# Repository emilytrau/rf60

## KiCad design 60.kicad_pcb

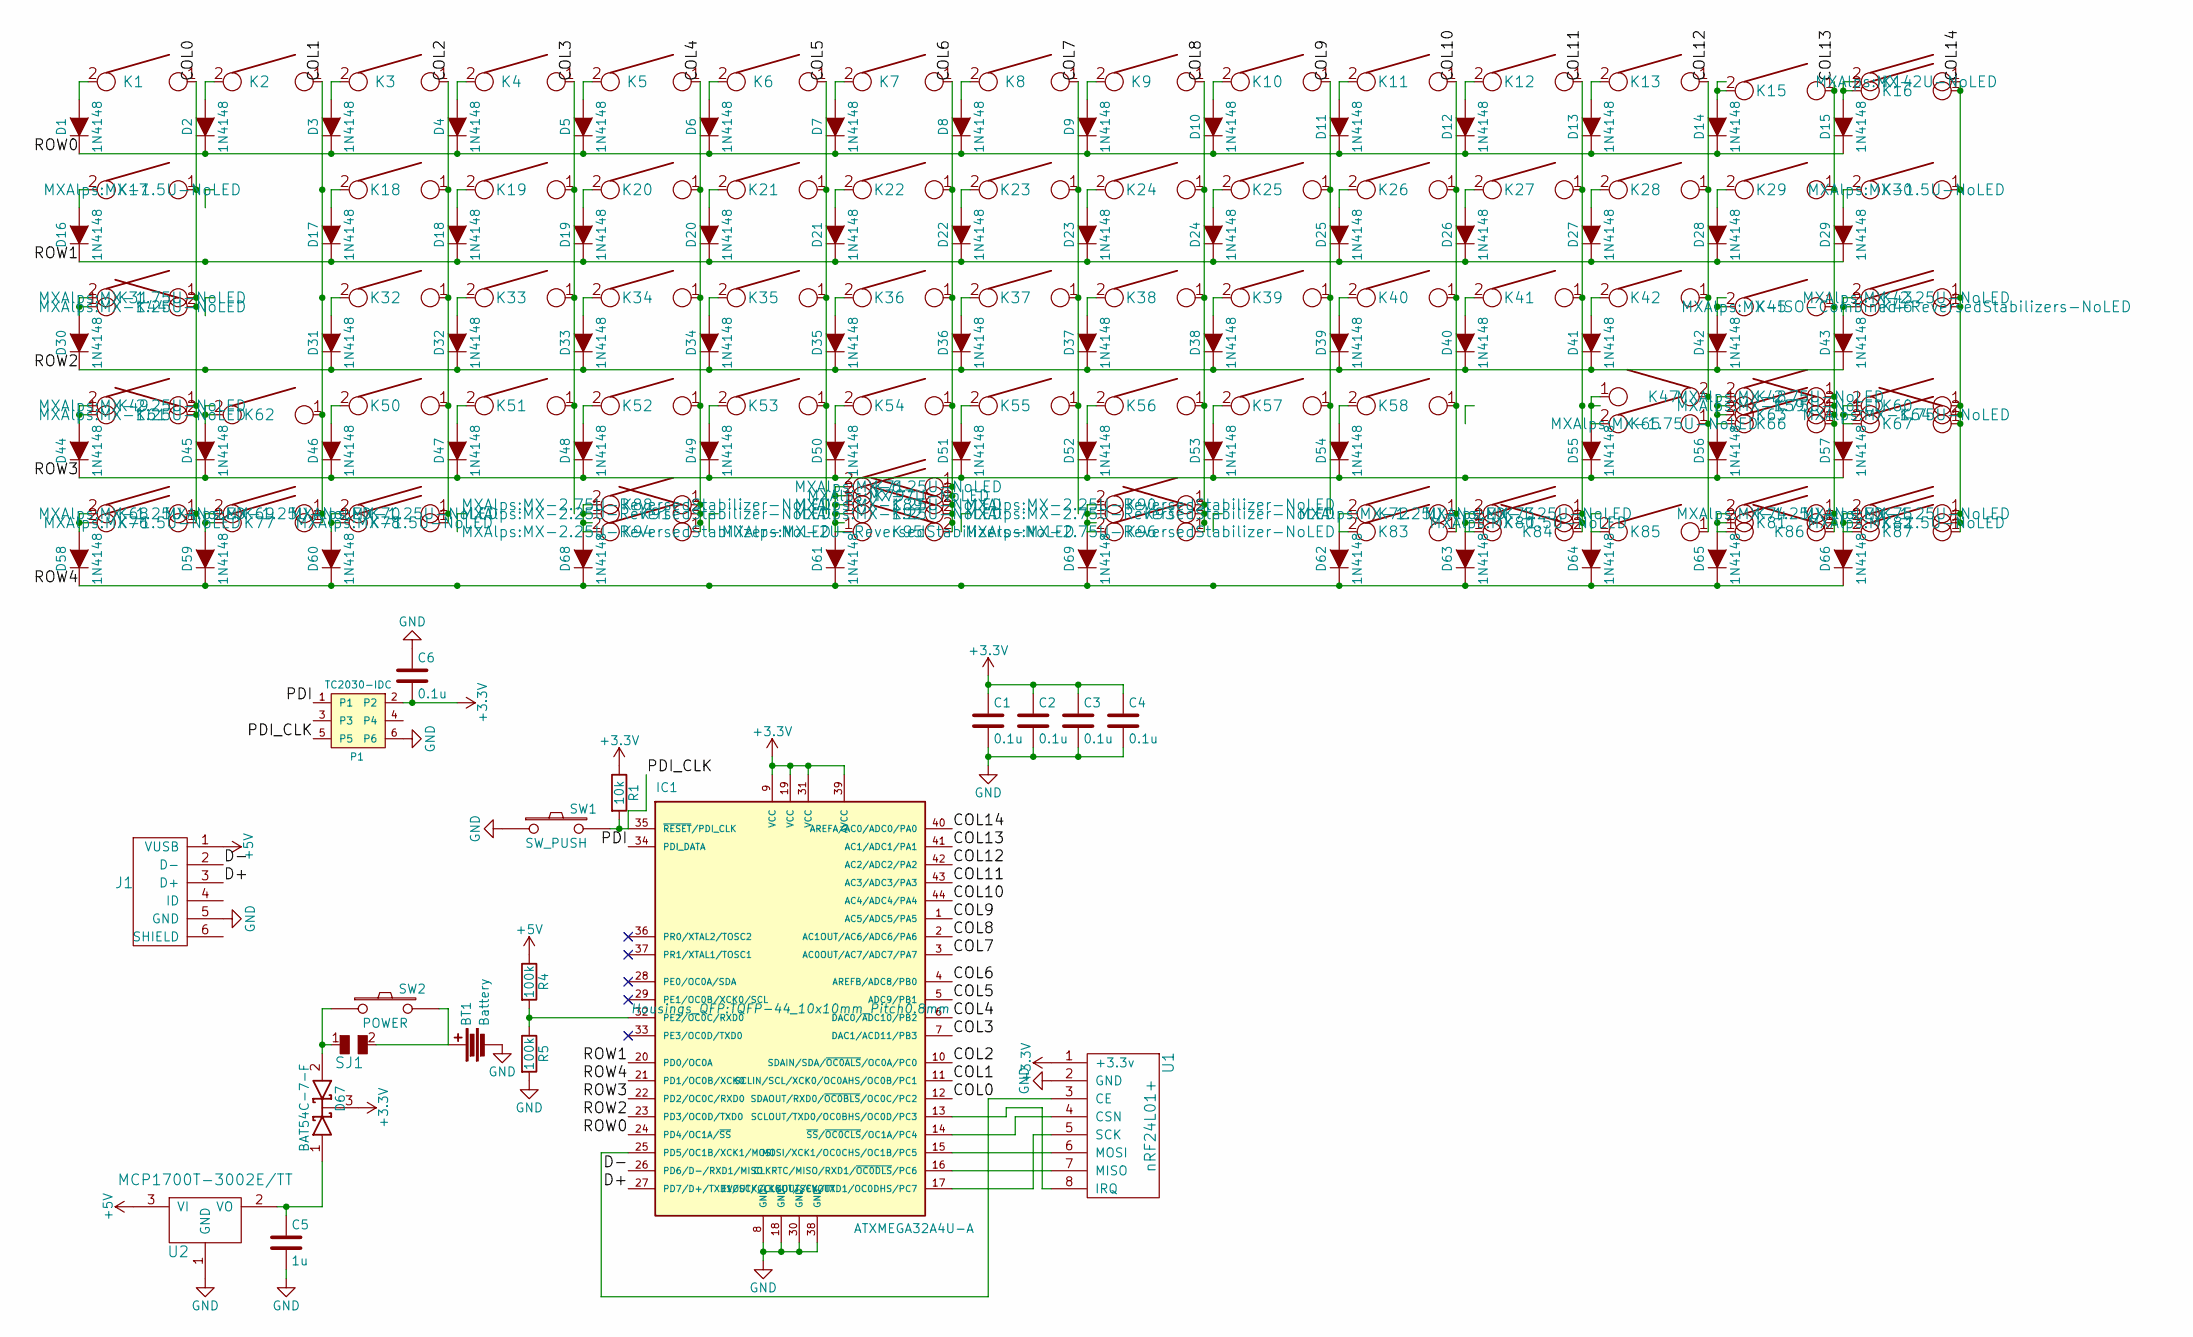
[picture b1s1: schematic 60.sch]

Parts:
BT1: Battery; CR2032_BK-913
C1, C2, C3, C4, C6: 0.1u; C_0805_HandSoldering
C5: 1u; C_0805_HandSoldering
D1, D2, D3, D4, D5, D6, D7, D8, D9, D10, D11, D12, D13, D14, D15, D16, D17, D18, D19, D20, D21, D22, D23, D24, D25, D26, D27, D28, D29, D30, D31, D32, D33, D34, D35, D36, D37, D38, D39, D40, D41, D42, D43, D44, D45, D46, D47, D48, D49, D50, D51, D52, D53, D54, D55, D56, D57, D58, D59, D60, D61, D62, D63, D64, D65, D66, D68, D69: 1N4148; D_SOD-323_HandSoldering
D67: BAT54C-7-F; SOT-23_Handsoldering
IC1: ATXMEGA32A4U-A; TQFP-44_10x10mm_Pitch0.8mm
J1: USB_mini_micro_B; USB_miniB_hirose_5S8
K1, K2, K3, K4, K5, K6, K7, K8, K9, K10, K11, K12, K13, K15, K16, K18, K19, K20, K21, K22, K23, K24, K25, K26, K27, K28, K29, K32, K33, K34, K35, K36, K37, K38, K39, K40, K41, K42, K45, K47, K50, K51, K52, K53, K54, K55, K56, K57, K58, K60, K62, K63, K66, K67, K77, K81, K83, K84, K85, K86, K87: KEYSW; MX-1U-NoLED
K14: KEYSW; MX-2U-NoLED
K17, K30, K76, K78, K80, K82: KEYSW; MX-1.5U-NoLED
K31, K59, K64, K65: KEYSW; MX-1.75U-NoLED
K43, K49: KEYSW; MX-2.25U-NoLED
K44, K61, K68, K69, K70, K72, K73, K74, K75, K89, K92: KEYSW; MX-1.25U-NoLED
K46: KEYSW; MX-ISO-Combined-ReversedStabilizers-NoLED
K48: KEYSW; MX-2.75U-NoLED
K71: KEYSW; MX-6.25U-NoLED
K79: KEYSW; MX-7U-NoLED
K88, K93, K96: KEYSW; MX-2.75U-ReversedStabilizer-NoLED
K90, K91, K94: KEYSW; MX-2.25U-ReversedStabilizer-NoLED
K95: KEYSW; MX-2U-ReversedStabilizers-NoLED
P1: TC2030-IDC; TC2030-NL_SMALL
R1: 10k; R_0805_HandSoldering
R4, R5: 100k; R_0805_HandSoldering
SJ1: SOLDER_JUMPER; SOLDER_JUMPER_2
SW1: SW_PUSH; SW_SPST_TL3342
SW2: POWER; Pin_Header_Straight_1x02_Pitch2.54mm
U1: nRF24L01+; nRF24L01+_SMD
U2: MCP1700T-3002E/TT; SOT-23_Handsoldering

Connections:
+3V3: C1.1, C2.1, C3.1, C4.1, C6.2, D67.3 (K), IC1.9 (VCC), IC1.19 (VCC), IC1.31 (VCC), IC1.39 (AVCC), P1.2, R1.1, U1.1 (+3.3v)
+5V: J1.1 (VUSB), R4.1, U2.3 (VI)
/COL0: IC1.12 (SDAOUT/RXD0/~OC0BLS~/OC0C/PC2), K1.1, K17.1, K31.1, K44.2, K49.1, K61.2, K68.1, K76.1
/COL1: IC1.11 (SCLIN/SCL/XCK0/OC0AHS/OC0B/PC1), K2.1, K62.1, K69.1, K77.1
/COL2: IC1.10 (SDAIN/SDA/~OC0ALS~/OC0A/PC0), K3.1, K18.1, K32.1, K50.1, K70.1, K78.1
/COL3: IC1.7 (DAC1/ACD11/PB3), K4.1, K19.1, K33.1, K51.1
/COL4: IC1.6 (DAC0/ADC10/PB2), K5.1, K20.1, K34.1, K52.1, K88.1, K91.2, K94.1
/COL5: IC1.5 (ADC9/PB1), K6.1, K21.1, K35.1, K53.1
/COL6: IC1.4 (AREFB/ADC8/PB0), K7.1, K22.1, K36.1, K54.1, K71.1, K79.1, K89.2, K92.2, K95.2
/COL7: IC1.3 (AC0OUT/AC7/ADC7/PA7), K8.1, K23.1, K37.1, K55.1
/COL8: IC1.2 (AC1OUT/AC6/ADC6/PA6), K9.1, K24.1, K38.1, K56.1, K90.1, K93.2, K96.1
/COL9: IC1.1 (AC5/ADC5/PA5), K10.1, K25.1, K39.1, K57.1
/COL10: IC1.44 (AC4/ADC4/PA4), K11.1, K26.1, K40.1, K58.1, K72.1, K83.1
/COL11: IC1.43 (AC3/ADC3/PA3), K12.1, K27.1, K41.1, K73.1, K80.1, K84.2
/COL12: IC1.42 (AC2/ADC2/PA2), K13.1, K28.1, K42.1, K47.2, K65.1, K85.1
/COL13: IC1.41 (AC1/ADC1/PA1), K15.1, K29.1, K45.1, K48.1, K59.2, K63.1, K66.1, K74.1, K81.1, K86.2
/COL14: IC1.40 (AREFA/AC0/ADC0/PA0), K14.1, K16.1, K30.1, K43.1, K46.1, K60.1, K64.2, K67.1, K75.1, K82.1, K87.1
/D+: IC1.27 (PD7/D+/TXD1/SCK/CLKOUT/EVOUT), J1.3 (D+)
/D-: IC1.26 (PD6/D-/RXD1/MISO), J1.2 (D-)
/PDI: IC1.34 (PDI_DATA), P1.1
/PDI_CLK: IC1.35 (~RESET~/PDI_CLK), P1.5, R1.2, SW1.2
/ROW0: D1.1 (K), D2.1 (K), D3.1 (K), D4.1 (K), D5.1 (K), D6.1 (K), D7.1 (K), D8.1 (K), D9.1 (K), D10.1 (K), D11.1 (K), D12.1 (K), D13.1 (K), D14.1 (K), D15.1 (K), IC1.24 (PD4/OC1A/~SS~)
/ROW1: D16.1 (K), D17.1 (K), D18.1 (K), D19.1 (K), D20.1 (K), D21.1 (K), D22.1 (K), D23.1 (K), D24.1 (K), D25.1 (K), D26.1 (K), D27.1 (K), D28.1 (K), D29.1 (K), IC1.20 (PD0/OC0A)
/ROW2: D30.1 (K), D31.1 (K), D32.1 (K), D33.1 (K), D34.1 (K), D35.1 (K), D36.1 (K), D37.1 (K), D38.1 (K), D39.1 (K), D40.1 (K), D41.1 (K), D42.1 (K), D43.1 (K), IC1.23 (PD3/OC0D/TXD0)
/ROW3: D44.1 (K), D45.1 (K), D46.1 (K), D47.1 (K), D48.1 (K), D49.1 (K), D50.1 (K), D51.1 (K), D52.1 (K), D53.1 (K), D54.1 (K), D55.1 (K), D56.1 (K), D57.1 (K), IC1.22 (PD2/OC0C/RXD0)
/ROW4: D58.1 (K), D59.1 (K), D60.1 (K), D61.1 (K), D62.1 (K), D63.1 (K), D64.1 (K), D65.1 (K), D66.1 (K), D68.1 (K), D69.1 (K), IC1.21 (PD1/OC0B/XCK0)
GND: BT1.2, C1.2, C2.2, C3.2, C4.2, C5.2, C6.1, IC1.8 (GND), IC1.18 (GND), IC1.30 (GND), IC1.38 (GND), J1.5 (GND), P1.6, R5.2, SW1.1, U1.2 (GND), U2.1 (GND)
unnamed: BT1.1, SJ1.2, SW2.2
unnamed: C5.1, D67.1 (A), U2.2 (VO)
unnamed: D1.2 (A), K1.2
unnamed: D2.2 (A), K2.2
unnamed: D3.2 (A), K3.2
unnamed: D4.2 (A), K4.2
unnamed: D5.2 (A), K5.2
unnamed: D6.2 (A), K6.2
unnamed: D7.2 (A), K7.2
unnamed: D8.2 (A), K8.2
unnamed: D9.2 (A), K9.2
unnamed: D10.2 (A), K10.2
unnamed: D11.2 (A), K11.2
unnamed: D12.2 (A), K12.2
unnamed: D13.2 (A), K13.2
unnamed: D14.2 (A), K15.2
unnamed: D15.2 (A), K14.2, K16.2
unnamed: D16.2 (A), K17.2
unnamed: D17.2 (A), K18.2
unnamed: D18.2 (A), K19.2
unnamed: D19.2 (A), K20.2
unnamed: D20.2 (A), K21.2
unnamed: D21.2 (A), K22.2
unnamed: D22.2 (A), K23.2
unnamed: D23.2 (A), K24.2
unnamed: D24.2 (A), K25.2
unnamed: D25.2 (A), K26.2
unnamed: D26.2 (A), K27.2
unnamed: D27.2 (A), K28.2
unnamed: D28.2 (A), K29.2
unnamed: D29.2 (A), K30.2
unnamed: D30.2 (A), K31.2, K44.1
unnamed: D31.2 (A), K32.2
unnamed: D32.2 (A), K33.2
unnamed: D33.2 (A), K34.2
unnamed: D34.2 (A), K35.2
unnamed: D35.2 (A), K36.2
unnamed: D36.2 (A), K37.2
unnamed: D37.2 (A), K38.2
unnamed: D38.2 (A), K39.2
unnamed: D39.2 (A), K40.2
unnamed: D40.2 (A), K41.2
unnamed: D41.2 (A), K42.2
unnamed: D42.2 (A), K45.2
unnamed: D43.2 (A), K43.2, K46.2
unnamed: D44.2 (A), K49.2, K61.1
unnamed: D45.2 (A), K62.2
unnamed: D46.2 (A), K50.2
unnamed: D47.2 (A), K51.2
unnamed: D48.2 (A), K52.2
unnamed: D49.2 (A), K53.2
unnamed: D50.2 (A), K54.2
unnamed: D51.2 (A), K55.2
unnamed: D52.2 (A), K56.2
unnamed: D53.2 (A), K57.2
unnamed: D54.2 (A), K58.2
unnamed: D55.2 (A), K47.1, K65.2
unnamed: D56.2 (A), K48.2, K59.1, K63.2, K66.2
unnamed: D57.2 (A), K60.2, K64.1, K67.2
unnamed: D58.2 (A), K68.2, K76.2
unnamed: D59.2 (A), K69.2, K77.2
unnamed: D60.2 (A), K70.2, K78.2
unnamed: D61.2 (A), K71.2, K79.2, K89.1, K92.1, K95.1
unnamed: D62.2 (A), K72.2, K83.2
unnamed: D63.2 (A), K73.2, K80.2, K84.1
unnamed: D64.2 (A), K85.2
unnamed: D65.2 (A), K74.2, K81.2, K86.1
unnamed: D66.2 (A), K75.2, K82.2, K87.2
unnamed: D67.2 (A), SJ1.1, SW2.1
unnamed: D68.2 (A), K88.2, K91.1, K94.2
unnamed: D69.2 (A), K90.2, K93.1, K96.2
unnamed: IC1.13 (SCLOUT/TXD0/OC0BHS/OC0D/PC3), U1.8 (IRQ)
unnamed: IC1.14 (~SS~/~OC0CLS~/OC1A/PC4), U1.4 (CSN)
unnamed: IC1.15 (MOSI/XCK1/OC0CHS/OC1B/PC5), U1.6 (MOSI)
unnamed: IC1.16 (CLKRTC/MISO/RXD1/~OC0DLS~/PC6), U1.7 (MISO)
unnamed: IC1.17 (EVOUT/CLKOUT/SCK/TXD1/OC0DHS/PC7), U1.5 (SCK)
unnamed: IC1.25 (PD5/OC1B/XCK1/MOSI), U1.3 (CE)
unnamed: IC1.32 (PE2/OC0C/RXD0), R4.2, R5.1

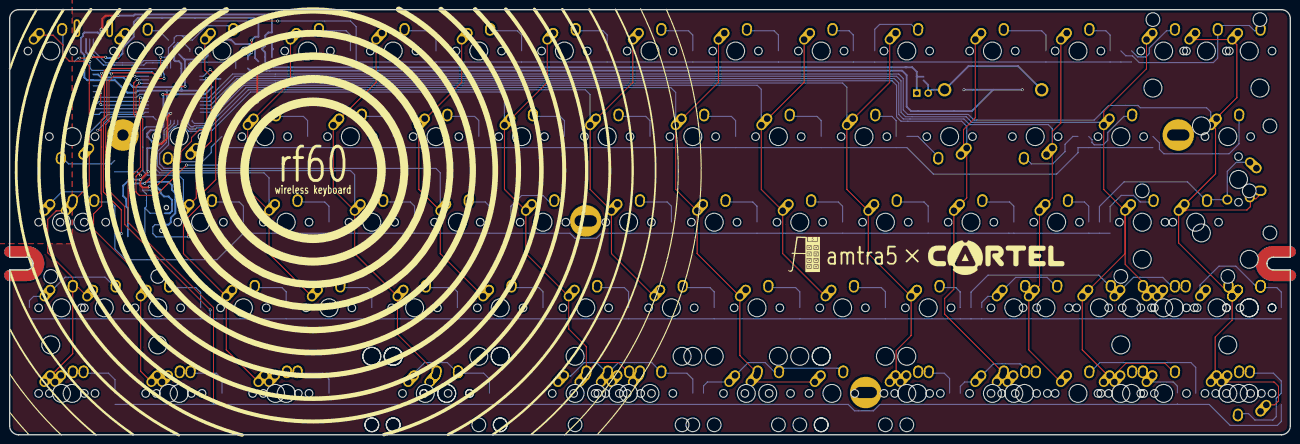
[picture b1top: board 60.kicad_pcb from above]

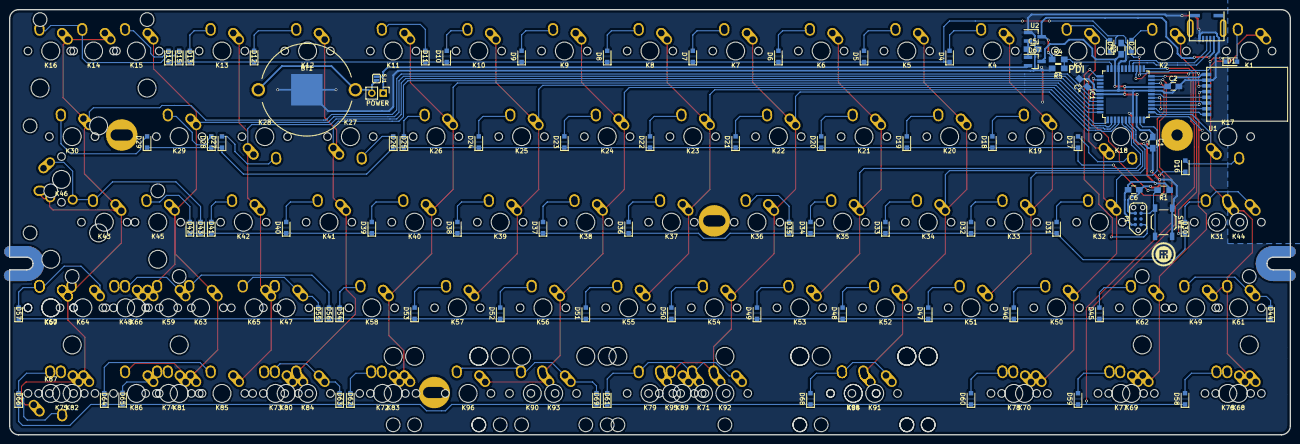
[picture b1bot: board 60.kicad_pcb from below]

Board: 2 copper layers, 285.0 x 94.6 mm, 183 parts (87 on the bottom side), 105 nets.

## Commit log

2017-10-23 Add submodules
2017-10-23 Laid out schematic matrix
2017-10-23 Updated submodule
2017-10-23 Placed switches and diodes
2017-10-25 pre-diode swap
2017-10-28 Added submodule
2017-10-28 Update submodule
2017-10-28 Finished PCB functionality
2017-10-28 Create LICENSE
2017-10-28 Add fuse
2017-10-29 Begin decorating
2017-10-31 Finish frontsize deco
2018-01-13 Prototype 1
2018-01-13 Prototype 1 fix
    Fix tag connect and added airi
2018-01-16 Prototype 1 last fix
